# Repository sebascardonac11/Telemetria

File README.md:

# Telemetria
Repositorio para el sistema de telemetria de motos.

Sensor:
https://www.aliexpress.us/item/3256804723517743.html?spm=a2g0o.order_detail.order_detail_item.3.1545f19cQoQ1aQ&gatewayAdapt=glo2usa4itemAdapt≈

HTTPS:
https://github.com/esp8266/Arduino/blob/master/libraries/ESP8266HTTPClient/examples/BasicHttpsClient/BasicHttpsClient.ino

Server:
https://www.tecnologia-informatica.es/Servidor-web-con-nodemcu-esp8266/

Access Point:
https://randomnerdtutorials.com/esp8266-nodemcu-access-point-ap-web-server/

Feature:

4T
- ODB2
- GPS
- Suspention
- Tires Temperture
- Breake Pressure Sensor

2T
- Horometer
- Lambda Sensor
- RPMs
- Cylinder Temperture 
- GPS
- Suspention
- Tires Temperture
- Breake Pressure Sensor

FoodPrint MEGA PRO
https://www.snapeda.com/parts/Mega%20Pro%20Embed%20CH340G%20/%20ATmega2560/Robotdyn/view-part/?company=Independent&amp;welcome=home

FoodPrint Oled
https://github.com/pforrmi/KiCad-SSD1306-128x64/tree/master/library

Guia RPMs
https://microedu.es/Electronica/AprendiendoArduino/ContadorRPM/ContadorRPM.html

GPS
http://arduiniana.org/libraries/tinygpsplus/
https://github.com/mikalhart/TinyGPSPlus

Aliexpress
Conectores
https://www.aliexpress.us/item/3256805495780717.html?spm=a2g0o.productlist.main.101.41be6a9bwBo6vh&algo_pvid=24ba319e-1bab-4e5a-8dd8-8dd42e3cdaf4&algo_exp_id=24ba319e-1bab-4e5a-8dd8-8dd42e3cdaf4-50&pdp_npi=4%40dis%21COP%2115408.11%2110014.99%21%21%2126.77%21%21%402101e9ec16923713259985716e9622%2112000033995415937%21sea%21CO%210%21A&curPageLogUid=ShYtpqijpnhq&gatewayAdapt=esp2usa4itemAdapt

Pantalla
https://www.aliexpress.us/item/2251832829271342.html?spm=a2g0o.detail.1000014.1.369163b1FpLUiy&gps-id=pcDetailBottomMoreOtherSeller&scm=1007.40050.281175.0&scm_id=1007.40050.281175.0&scm-url=1007.40050.281175.0&pvid=6631ef20-063d-47a6-b15a-3fde64870c59&_t=gps-id%3ApcDetailBottomMoreOtherSeller%2Cscm-url%3A1007.40050.281175.0%2Cpvid%3A6631ef20-063d-47a6-b15a-3fde64870c59%2Ctpp_buckets%3A668%232846%238109%231935&pdp_npi=4%40dis%21COP%2118254.81%2113135.07%21%21%214.35%21%21%402103251316923727307098682e7f25%2112000026583382486%21rec%21CO%21%21A&gatewayAdapt=esp2usa4itemAdapt

Oscilloscope
https://www.aliexpress.us/item/3256805644252314.html?spm=a2g0o.productlist.main.5.3455490e7AM4vD&algo_pvid=f8ce14f6-df39-4c0a-a28f-e726a152e160&algo_exp_id=f8ce14f6-df39-4c0a-a28f-e726a152e160-2&pdp_npi=4%40dis%21COP%21414413.21%21207206.6%21%21%21720.00%21%21%402103241d16923736754275295e2f43%2112000034503040413%21sea%21CO%210%21A&curPageLogUid=tnNOdzDNyeeZ&gatewayAdapt=esp2usa4itemAdapt

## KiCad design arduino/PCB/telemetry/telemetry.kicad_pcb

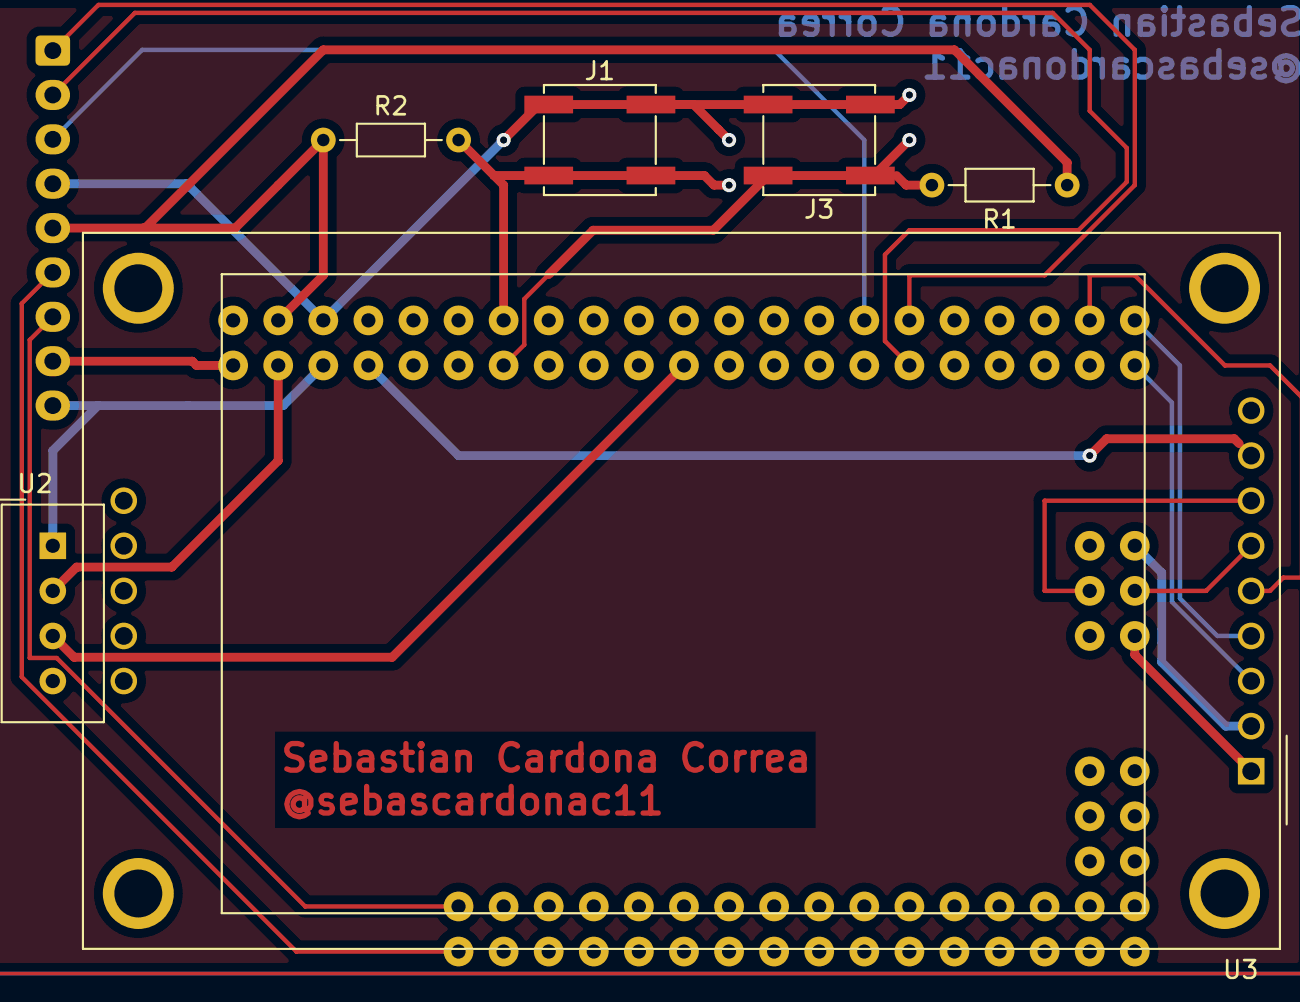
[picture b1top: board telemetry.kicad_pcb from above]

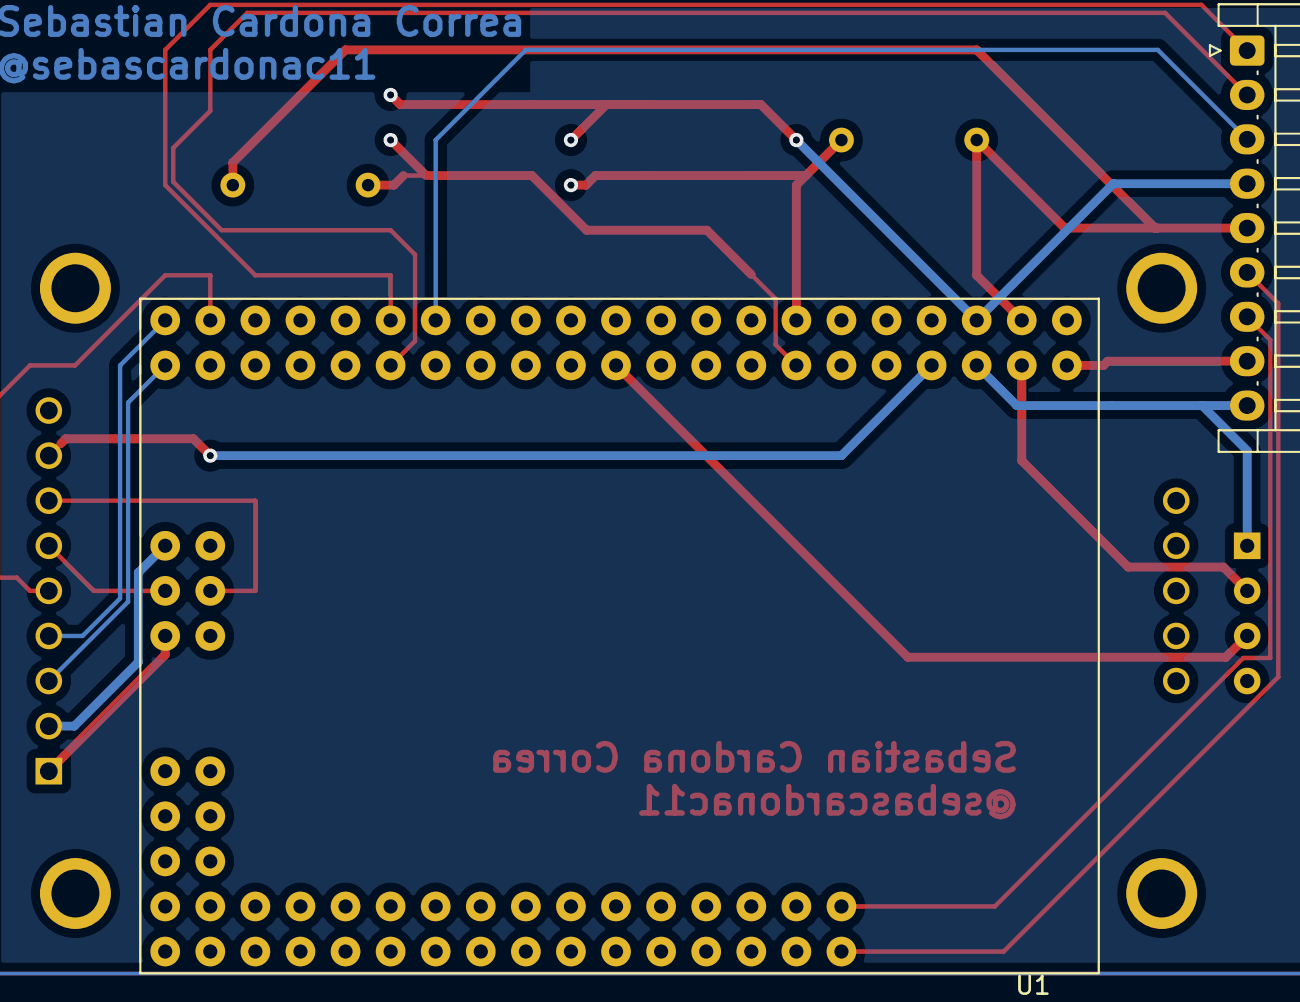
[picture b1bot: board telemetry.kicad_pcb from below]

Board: 2 copper layers, 8 parts (2 on the bottom side), 17 nets.

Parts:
J1: Boton Enter; SW_SPST_EVPBF
J3: Boton Next; SW_SPST_EVPBF
J4: DE9_Plug; JST_EH_S9B-EH_1x09_P2.50mm_Horizontal
R1, R2: R_Photo; R_Axial_DIN0204_L3.6mm_D1.6mm_P7.62mm_Horizontal
U1: MEGA_PRO_EMBED_CH340G_{slash}_ATMEGA2560; MODULE_MEGA_PRO_EMBED_CH340G___ATMEGA2560
U2: NEO-M8N; Aosong_DHT11_5.5x12.0_P2.54mm
U3: CR2013-MI2120

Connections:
+3.3V: U1.3V3_2 (3V3), U3.8 (LED)
+5V: J1.1, J3.2, J4.4, J4.9, U1.5V_1 (5V), U1.5V_2 (5V), U1.5V_3 (5V), U2.1 (~SAFEBOOT), U3.1 (VCC)
A0_Suspention: J4.6, U1.A0
A1_Suspention: J4.7, U1.A1
CS: U1.D30, U3.3 (~CS)
DC: U1.D29, U3.5 (D/~C)
GND: J4.5, R1.1, R2.1, U1.GND_1 (GND), U1.GND_2 (GND), U1.GND_3 (GND), U2.2 (D_SEL), U3.2 (GND)
unnamed: J1.2, R2.2, U1.D3
unnamed: J3.1, R1.2, U1.D2
unnamed: U1.MOSI, U3.6 (MOSI)
unnamed: U1.SCK, U3.7 (SCK)
RPM: J4.3, U1.D19
RST: U1.D31, U3.4 (RESET)
SCL: J4.1, U1.D21
SDA: J4.2, U1.D20
TX_GPS: U1.D10, U2.3 (TIMEPULSE)
VIN_2: J4.8, U1.VIN_2 (VIN)

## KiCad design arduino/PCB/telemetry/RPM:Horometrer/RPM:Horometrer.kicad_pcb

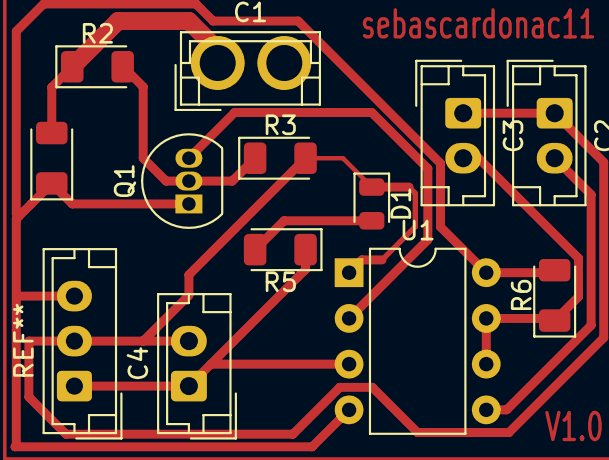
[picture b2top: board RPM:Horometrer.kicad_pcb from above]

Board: 2 copper layers, 12 parts (0 on the bottom side), 8 nets.

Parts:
C1: C; JST_EH_B2B-EH-A_1x02_P2.50mm_Vertical
C2, C3, C4: 100nF; JST_EH_B2B-EH-A_1x02_P2.50mm_Vertical
D1: LED; LED_0805_2012Metric
Q1: BC547; TO-92_Inline
R1, R2: 10K; D_1206_3216Metric
R3: 20K; D_1206_3216Metric
R5: 220; D_1206_3216Metric
R6: 17K; D_1206_3216Metric
U1: NE555P; DIP-8_W7.62mm

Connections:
+5V: Q1.1 (C), R1.1, R6.2, U1.4 (R), U1.8 (VCC)
GND: C2.1, C3.1, C4.2, D1.1 (K), R3.2, U1.1 (GND)
unnamed: C1.1, Q1.2 (B), R1.2, R2.1, R2.2, R3.1
unnamed: D1.2 (A), R5.2
unnamed: Q1.3 (E), U1.2 (TR)
unnamed: C2.2, U1.5 (CV)
unnamed: C3.2, R6.1, U1.6 (THR), U1.7 (DIS)
unnamed: C4.1, R5.1, U1.3 (Q)

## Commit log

2023-06-05 Version inicial
2023-06-07 Webpage
2023-06-07 Se incializa la aplicacion movil
2023-06-07 Se crea un login basico con los metodos de cognito para consumir la API de registro y login
2023-06-07 Update varials
2023-06-07 Se organizo la lista de motos traida de AWS
2023-06-07 Se pule el codigo para que solo haga un llamado a la libreria
2023-07-25 Actualizando codigo arduino de mega
2023-07-26 Generando pantalla LapTimer
2023-07-26 Optimizando laptimer y creando primera version de Session.
2023-08-03 Add RPM sensor
2023-08-04 Add RPM sensor to screen
2023-08-05 Add Session time
2023-08-10 Test with GPS NEO-M8N
2023-08-10 Calculate time based int ms
2023-08-16 Agregando objeto laps
2023-08-19 Add Feature of Revolutions
2023-09-17 Linear Sensor
2023-09-18 Good library to TFT Display
2023-09-28 Pantalla TFT funcionando Perfecto
2023-09-28 Update laptimerScreen
2023-10-05 Agregando Menu
2023-10-09 Fix UTC diference, Add summary of lap and show summary
2023-10-10 Fix lap time print
